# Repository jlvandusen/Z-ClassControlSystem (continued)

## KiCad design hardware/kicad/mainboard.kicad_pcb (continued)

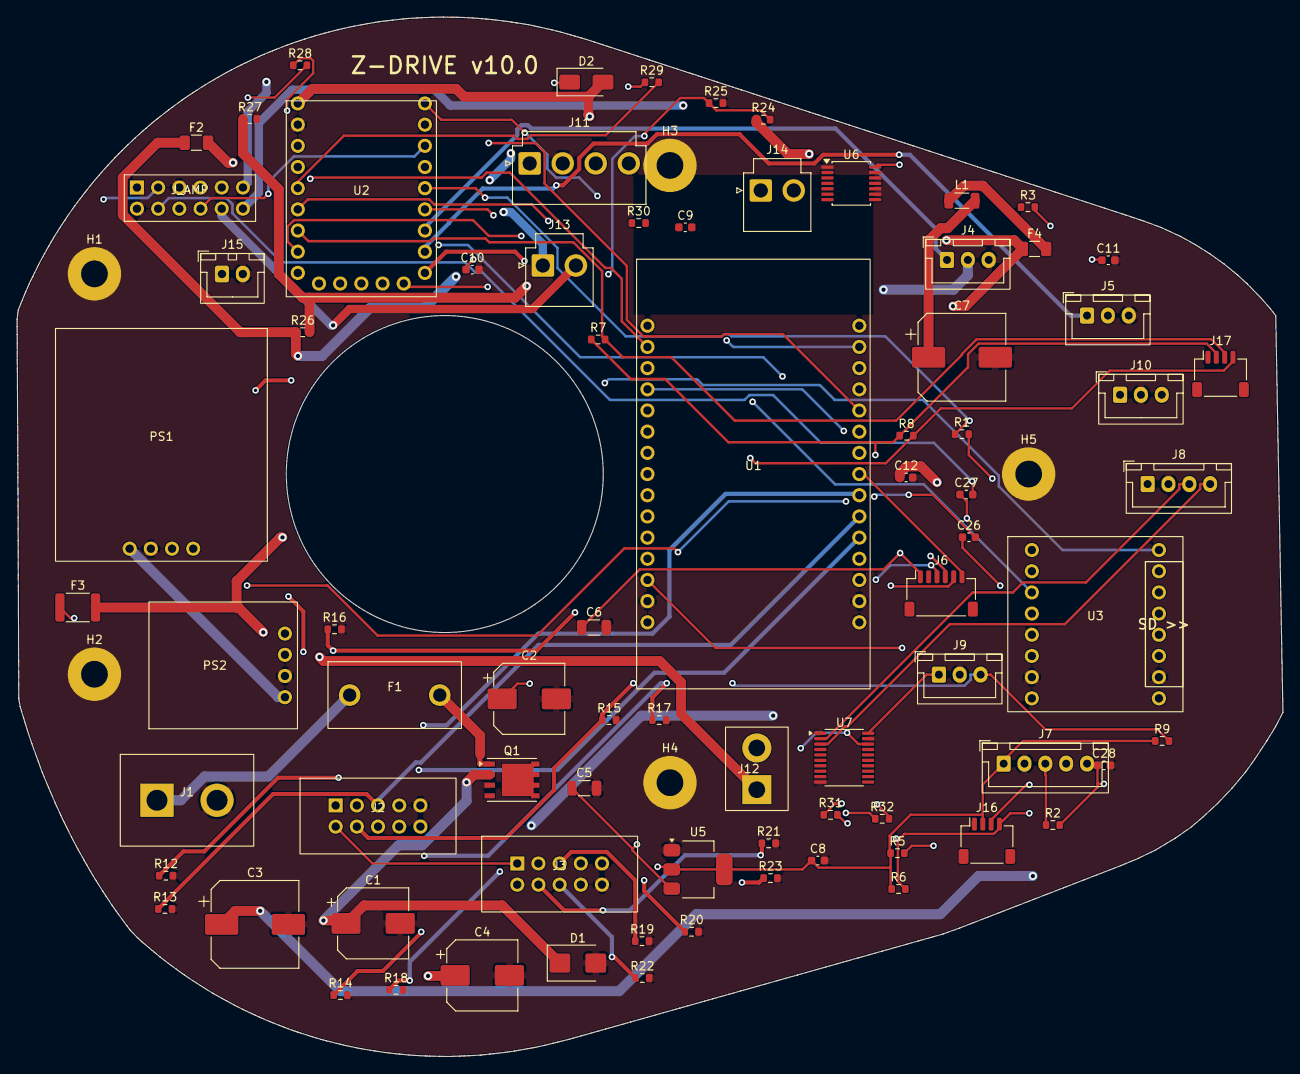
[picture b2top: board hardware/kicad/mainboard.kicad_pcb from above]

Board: 4 copper layers, 151.8 x 124.6 mm, 83 parts (0 on the bottom side), 67 nets.

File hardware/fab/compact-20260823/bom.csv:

Ref,Qty,Value / Part,MPN,Package,Supplier,Notes
U1,1,ESP-WROOM-32 DevKit (ELEGOO) - CUSTOMER FITS into J_U1A/J_U1B,ESP32-DevKit-V1 30-pin,plugs into 2x 1x15 sockets,Amazon B0D8T53CQ5,Drive MCU; 30-pin ONLY (38-pin is wider); antenna end toward H3
U2,1,Waveshare RP2350-Zero - CUSTOMER FITS into J_U2A/B/C,RP2350-Zero,plugs into 2x 1x9 + 1x5 sockets,Amazon B0DYTVCF2H,Body co-processor
U3,1,DFPlayer Mini,DFR0299,2x8 0.1in,DFRobot / AliExpress,SD MP3 source; socket
U4,1,MAX9744 class-D amp,MAX9744ETH+,TQFN-44 7x7,Digi-Key,2x20W I2C volume; thermal pad to pour
U5,1,3.3V 1A LDO,AMS1117-3.3,SOT-223,LCSC C6186,Pinout GND/OUT(tab)/IN as routed. Alt AP7361C-33ER-13 (SOT-223R, C3743528). NOT AP7361C-33E-13 (IN/GND/OUT - wrong for this board)
U6,1,NeoPixel level shifter,74AHCT125PW,TSSOP-14,Digi-Key,3.3->5V WS2812 data
U7,1,Encoder level shifter,74LVC245APW,TSSOP-20,Digi-Key,5V encoder A/B -> 3.3V (or 2x BSS138)
PS1,1,5V 5A buck module,Pololu D24V50F5,Pololu 5-pin row EN VIN GND GND OUT,Pololu 2851,+5V_LOGIC and +5V_LED
PS2,1,6V 2.5A buck module,Pololu D24V25F6,Pololu 5-pin row EN VIN GND GND OUT,Pololu 2852,+6V_SERVO: 6.0 V suits BOTH Hitec HS-805BB (4.8-6V) and JX PDI-HV2060MG (6-8.4V)
Q1,1,P-FET reverse polarity (high-side RPP),SI7461DP-T1-GE3,PowerPAK SO-8,Digi-Key,"-60V 14.5mOhm -14A; pads 1-3 S=VIN, 4 G, 5 tab D=BAT_F"
D1,1,TVS,SMBJ15A,SMB,Digi-Key,Input clamp 12V pack
D2,1,Schottky,SS14,SMA,Digi-Key,+5V_LOGIC -> RP2350-Zero 5V (USB back-feed block); pad1 K = RP_5V
D6,1,Zener 12V (Q1 gate clamp),BZT52C12-7-F,SOD-123,Digi-Key,VGS clamp S->G
D4,1,BAT54S,BAT54S,SOT-23,Digi-Key,ADC clamp on VBAT_SENSE (GPIO35); pin1 A->GND pin2 K->3V3 pin3 COM->sense
F1,1,Mini blade fuse holder + 10A ATM fuse,Keystone 3568 / 10A ATM,THT 9.9mm pitch,LCSC C5249699 / auto store,Board input (bucks + amp only; motors fed from the pack directly)
F3,1,Polyfuse 3A,MF-MSMF300,1812,Digi-Key,+5V_LED to slip ring
F4,1,Fuse 3A fast (amp 12V),0466003.NR,1206,Digi-Key,Littelfuse 466 series 32V
L1,1,Ferrite bead 600R@100MHz 2.9A,BLM31KN601SN1L,1206,LCSC C668306,Amp supply (PG variant is only 1.5 A)
C1,1,220uF 25V electrolytic,EEE-FK1E221P,SMD 8x10,Digi-Key,VIN
C2,1,470uF 10V,EEE-FK1A471P,SMD 8x10,Digi-Key,+5V_LOGIC
C3,1,1000uF 10V,EEE-FK1A102P,SMD 10x10,Digi-Key,+5V_LED
C4,1,470uF 16V,EEE-FK1C471P,SMD 8x10,Digi-Key,+6V_SERVO
C7,1,1000uF 25V,EEE-FP1E102AP,SMD 10x10.2,Digi-Key,MAX9744 supply (10mm can to match CP_Elec_10x10; verify height vs casing)
C5-C6,2,10uF 25V X7R,GRM31CR71E106KA12L,1206,Digi-Key,Rail local (+5V_LOGIC / +3V3)
C8-C25 + C29,19,100nF 50V X7R,CL10B104KB8NNNC,0603,Digi-Key,Decoupling; C29 = VBAT_SENSE ADC reservoir
C26-C27,2,1uF 16V X7R,CL10B105KO8NNNC,0603,Digi-Key,Audio input coupling
C28,1,100nF,CL10B104KB8NNNC,0603,Digi-Key,Pot / AS5600 OUT filter
R1,1,1k 1%,RC0603FR-071KL,0603,Digi-Key,DFPlayer TX series
R2,1,1k 1%,RC0603FR-071KL,0603,Digi-Key,Pot/AS5600 OUT series
R3-R4,2,330R 1%,RC0603FR-07330RL,0603,Digi-Key,NeoPixel data series (body + spare)
R5-R8,4,4.7k 1%,RC0603FR-074K7L,0603,Digi-Key,I2C pull-ups (ESP32 bus + RP2350 bus)
R9-R11,3,10k 1%,RC0603FR-0710KL,0603,Digi-Key,Hall / encoder pull-ups
R12-R23,12,10k 1%,RC0603FR-0710KL,0603,Digi-Key,Motor driver PWM/INA/INB pull-downs (4 ch x 3)
R24,1,47k 1%,RC0603FR-0747KL,0603,Digi-Key,Battery sense top
R25,1,10k 1%,RC0603FR-0710KL,0603,Digi-Key,Battery sense bottom
R28,1,10k 1%,RC0603FR-0710KL,0603,Digi-Key,ESTOP pull-up
R29-R30,2,10k 1%,RC0603FR-0710KL,0603,Digi-Key,+5V_LOGIC sense divider (RP2350 GP28)
R33,1,47k 1%,RC0603FR-0747KL,0603,Digi-Key,Q1 gate pull-down
J1,1,XT60 male PCB VERTICAL,XT60PB-M (Amass),THT 2x dia4.0 @ 7.2mm,LCSC C19268037 (alt JLC lib C9900017179),SINGLE board VCC input: 12 V 3S4P pack (9-12.6 V) -> F1 10A -> Q1 RPP -> VIN; pack lead = XT60 female
J_AMP,1,Pin header 2x7 0.1in male,PH2-14-UA,TH,Digi-Key,MAX9744 amp module harness: 1 VDD12 2 GND 3 INL 4 INR 5 AGND 6 SDA 7 SCL 8 SHDN 9-12 SPK L+/L-/R+/R- 13 Vi2c(3V3) 14 GND
J_U1A-J_U1B,2,Female header 1x15 2.54mm 8.5mm,B-2200S15P-A120 (Ckmtw),THT,LCSC C124408,ESP32 DevKitC sockets
J_U2A-J_U2B,2,Female header 1x9 2.54mm 8.5mm,B-2200S09P-A120 (Ckmtw),THT,LCSC C124417,RP2350-Zero side sockets (low stock: cut a 1x15 if out)
J_U2C,1,Female header 1x5 2.54mm 8.5mm,2.54-1*5P (BOOMELE),THT,LCSC C50950,RP2350-Zero end socket
J2-J3,2,Pin header 2x5 0.1in male (no shroud),PH2-10-UA,TH,Digi-Key,Motor driver IDC ribbons - odd pins = channel A row (VCC PWM INA INB GND); even = channel B
J4-J5,2,Pin header 1x3 0.1in,PH1-03-UA,TH,Digi-Key,Servos L / R (SIG +6V GND) - Hitec HS-805BB or JX PDI-HV2060MG jumbo servos
J6,1,JST-XH 4-pin,B4B-XH-A,XH TH,Digi-Key,IMU GY-BMI160 over I2C: 1 +5V->VIN, 2 GND, 3 SCL, 4 SDA (same order as v9.15 MPU)
J7,1,JST-XH 5-pin,B5B-XH-A,XH TH,Digi-Key,S2S sensor (3V3 GND OUT SDA SCL) - AS5600 or pot
J8,1,JST-XH 4-pin,B4B-XH-A,XH TH,Digi-Key,Dome encoder (B A GND 5V) - same order as v9.15 DOME_ENC
J9,1,JST-XH 3-pin,B3B-XH-A,XH TH,Digi-Key,Hall
J10,1,JST-XH 3-pin,B3B-XH-A,XH TH,Digi-Key,Body NeoPixel (5V GND DATA)
J11,1,JST-XH 2-pin,B2B-XH-A,XH TH,Digi-Key,Slip ring: +5V_LED / GND to body-shell NeoPixels (pack charges via its own lead - no charge path on board)
J13-J14,2,JST-VH 2-pin,B2P-VH,VH TH,Digi-Key,Speakers L / R (BTL)
J15,1,JST-XH 2-pin,B2B-XH-A,XH TH,Digi-Key,ESTOP loop
J17,1,JST-SH 4-pin (Qwiic),SM04B-SRSS-TB,SH SMD,Digi-Key,I2C expansion on the RP2350 bus (ESP32 bus is on J7 pins 4/5)
SW1,1,Tactile (RP2350 / board reset),PTS645SK50SMTR92,SMD,Digi-Key,Optional
TP1-TP10,10,Test points,5019,SMD,Digi-Key,3V3 5V_LOGIC 5V_LED 6V VIN UART x2 MOTOR_EN
H1-H4,4,M3 mounting holes,-,3.2mm,-,Reuse v9.15 pattern if on the deck
PCB,1,4-layer 1oz 1.6mm FR4 (F/In1 GND/In2 +5V/B),-,-,PCBWay,teardrop ~152x125 (extended) or ~152x110 (compact)

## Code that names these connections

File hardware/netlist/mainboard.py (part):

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A(dict(ref="J1", value="XT60PB-M vertical", kind="connector", fp="Connector_AMASS:AMASS_XT60-M_1x02_P7.20mm_Vertical",
       at=(-27, -31), rot=0, side="F", pins=[(1,"+","BAT+"),(2,"-","GND")]))
A(dict(ref="F1", value="10A blade fuse", kind="fuse", fp="ZCLASS:Fuse_Mini_Blade",
       at=(-13, -26.5), rot=0, side="F", pins=[(1,"1","BAT+"),(2,"2","BAT_F")]))
# High-side reverse-polarity P-FET. PowerPAK SO-8 pinout: pads 1,2,3 = SOURCE, 4 = GATE,
# 5 = DRAIN (tab). RPP orientation: D = battery side (BAT_F), S = load side (VIN);
# body diode pre-charges VIN, then VGS = -VIN enhances; a reversed pack is blocked.
# Si7461DP: -60 V, 14.5 mOhm, -14 A (SQJ431EP was 213 mOhm and an SO-8L part - wrong).
A(dict(ref="Q1", value="Si7461DP P-FET RPP", kind="ic3", fp="Package_SO:PowerPAK_SO-8_Single",
       at=(-1, -26), rot=0, side="F",
       pins=[(1,"S","VIN"),(2,"S","VIN"),(3,"S","VIN"),(4,"G","Q1_G"),(5,"D","BAT_F")]))
# gate protection: VGS clamped to -12 V (abs max +/-20 V; SMBJ15A can let VIN reach ~24 V)
A(two("D6", "BZT52C12 12V zener", "diode", "Diode_SMD:D_SOD-123", (-1, -22), "VIN", "Q1_G"))   # pin1 K = VIN (source), pin2 A = gate
A(two("R33", "47k", "res", "Resistor_SMD:R_0603_1608Metric", (3, -22), "Q1_G", "GND"))
A(two("D1", "SMBJ15A", "diode", "Diode_SMD:D_SMB", (8, -22.5), "VIN", "GND"))
A(two("C1", "220u/25V", "cap", "Capacitor_SMD:CP_Elec_8x10", (-32, -19), "VIN", "GND"))
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# ADC protection (GPIO35 is input-only, no internal clamps): BAT54S series pair in SOT-23,
# pin1 = A1 -> GND, pin2 = K2 -> +3V3, pin3 = common -> sense node. Plus 100n (SAR ADC charge reservoir).
A(dict(ref="D4", value="BAT54S", kind="ic3", fp="Package_TO_SOT_SMD:SOT-23", at=(47, 38), rot=0, side="F",
       pins=[(1,"A1","GND"),(2,"K2","+3V3"),(3,"COM","VBAT_SENSE")]))
A(two("C29", "100n", "cap", "Capacitor_SMD:C_0603_1608Metric", (44, 37), "VBAT_SENSE", "GND"))
# ---- 5V / 3V3 rail parts
A(two("C2", "470u/10V", "cap", "Capacitor_SMD:CP_Elec_8x10", (-26, -19), "+5V_LOGIC", "GND"))
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# ---- servos: 6.0 V rail = the one voltage both the Hitec HS-805BB (4.8-6.0 V) and the
#      JX PDI-HV2060MG (6.0-8.4 V) accept. Both are jumbo (1/4-scale) cases.
A(dict(ref="J4", value="Servo L", kind="connector", fp="Connector_PinHeader_2.54mm:PinHeader_1x03_P2.54mm_Vertical",
       at=(55, 21), rot=0, side="F", pins=[(1,"SIG","SERVO_L"),(2,"6V","+6V_SERVO"),(3,"GND","GND")]))
A(dict(ref="J5", value="Servo R", kind="connector", fp="Connector_PinHeader_2.54mm:PinHeader_1x03_P2.54mm_Vertical",
       at=(66, 19), rot=0, side="F", pins=[(1,"SIG","SERVO_R"),(2,"6V","+6V_SERVO"),(3,"GND","GND")]))
# ---- IMU (I2C, 4-pin JST-XH like v9.15)
# IMU: GY-BMI160 breakout over I2C (ESP32 I2C-A bus, shared with the AS5600 - addr 0x68/0x69 vs 0x36).
# JST-XH 4-pin in the SAME order as the v9.15 "MPU" connector: VCC GND sig sig -> the old cable fits.
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# CS / SA0 left open -> I2C mode. The ESP32 SPI pins (D5/D18/D19/D23) are now spare.
A(dict(ref="J6", value="IMU BMI160 I2C", kind="connector", fp="Connector_JST:JST_XH_B4B-XH-A_1x04_P2.50mm_Vertical",
       at=(57, -24), rot=0, side="F",
       pins=[(1,"5V","+5V_LOGIC"),(2,"GND","GND"),(3,"SCL","I2C_A_SCL"),(4,"SDA","I2C_A_SDA")]))
# ---- S2S sensor (AS5600 or pot): 3V3 GND OUT SDA SCL
A(dict(ref="J7", value="S2S AS5600/pot", kind="connector", fp="Connector_JST:JST_XH_B5B-XH-A_1x05_P2.50mm_Vertical",
       at=(70, -19), rot=0, side="F",
       pins=[(1,"3V3","+3V3"),(2,"GND","GND"),(3,"OUT","S2S_OUT"),(4,"SDA","I2C_A_SDA"),(5,"SCL","I2C_A_SCL")]))
A(two("R2", "1k", "res", "Resistor_SMD:R_0603_1608Metric", (64, -30), "S2S_OUT", "S2S_POS"))
A(two("C28", "100n", "cap", "Capacitor_SMD:C_0603_1608Metric", (67, -30), "S2S_POS", "GND"))
# ---- dome encoder (5V) -> 74LVC245 -> 3V3
#   pin order kept IDENTICAL to the v9.15 DOME_ENC header (B, A, GND, VCC) so the
#   existing NeveRest encoder cable plugs straight in — do not reorder.
A(dict(ref="J8", value="Dome encoder", kind="connector", fp="Connector_JST:JST_XH_B4B-XH-A_1x04_P2.50mm_Vertical",
       at=(82, -14), rot=0, side="F", pins=[(1,"B","ENC_B_5V"),(2,"A","ENC_A_5V"),(3,"GND","GND"),(4,"5V","+5V_LOGIC")]))
A(dict(ref="U7", value="74LVC245A", kind="ic_generic", fp="Package_SO:TSSOP-20_4.4x6.5mm_P0.65mm",
       at=(30, -32), rot=0, side="F",
       # DIR HIGH = A->B (TI SN74LVC245A pin table). Encoder 5V sits on A1/A2, RP2350 on B1/B2, so DIR
       # must be +3V3 — it was GND (B->A) on the first rev-A gerbers (r6); fixed in r7. Unused A3..A8
       # are inputs when DIR=H, so they are tied to GND rather than left floating.
       pins=[(1,"DIR","+3V3"),(2,"A1","ENC_A_5V"),(3,"A2","ENC_B_5V"),(4,"A3","GND"),(5,"A4","GND"),(6,"A5","GND"),(7,"A6","GND"),(8,"A7","GND"),(9,"A8","GND"),
             (10,"GND","GND"),(11,"B8","NC"),(12,"B7","NC"),(13,"B6","NC"),(14,"B5","NC"),(15,"B4","NC"),(16,"B3","NC"),(17,"B2","ENC_B_3V3"),(18,"B1","ENC_A_3V3"),
             (19,"OE","GND"),(20,"VCC","+3V3")]))
A(two("C8", "100n", "cap", "Capacitor_SMD:C_0603_1608Metric", (30, -36), "+3V3", "GND"))
# ---- hall
A(dict(ref="J9", value="Hall", kind="connector", fp="Connector_JST:JST_XH_B3B-XH-A_1x03_P2.50mm_Vertical",
       at=(60, -30), rot=0, side="F", pins=[(1,"3V3","+3V3"),(2,"GND","GND"),(3,"SIG","HALL")]))
A(two("R9", "10k", "res", "Resistor_SMD:R_0603_1608Metric", (86, -30), "+3V3", "HALL"))
# ---- body NeoPixel: GP14 -> 74AHCT125 -> 330R -> J10
A(dict(ref="U6", value="74AHCT125", kind="ic_generic", fp="Package_SO:TSSOP-14_4.4x5mm_P0.65mm",
       at=(40, 30), rot=0, side="F",
       pins=[(1,"1OE","GND"),(2,"1A","NEO_3V3"),(3,"1Y","NEO_5V"),(4,"2OE","GND"),(5,"2A","GND"),(6,"2Y","NC"),(7,"GND","GND"),
             (8,"3Y","NC"),(9,"3A","GND"),(10,"3OE","GND"),(11,"4Y","NC"),(12,"4A","GND"),(13,"4OE","GND"),(14,"VCC","+5V_LOGIC")]))
A(two("C9", "100n", "cap", "Capacitor_SMD:C_0603_1608Metric", (40, 34), "+5V_LOGIC", "GND"))
A(two("R3", "330R", "res", "Resistor_SMD:R_0603_1608Metric", (47, 30), "NEO_5V", "NEO_OUT"))
A(dict(ref="J10", value="Body NeoPixel", kind="connector", fp="Connector_JST:JST_XH_B3B-XH-A_1x03_P2.50mm_Vertical",
       at=(77, 14), rot=0, side="F", pins=[(1,"5V","+5V_LED"),(2,"GND","GND"),(3,"DATA","NEO_OUT")]))
# ---- slip ring: +5V_LED + GND out to the body-shell NeoPixels only.
#      (The pack charges through its OWN charge lead, routed out through the axle -
#       the board carries no charge path and no charger sense.)
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       at=(-30, 38), rot=0, side="F", pins=[(1,"+","SPK_R+"),(2,"-","SPK_R-")]))
# ---- ESTOP loop
A(dict(ref="J15", value="ESTOP", kind="connector", fp="Connector_JST:JST_XH_B2B-XH-A_1x02_P2.50mm_Vertical",
       at=(6, 47), rot=0, side="F", pins=[(1,"LOOP","ESTOP_SENSE"),(2,"GND","GND")]))
A(two("R28", "10k", "res", "Resistor_SMD:R_0603_1608Metric", (-30, 46), "+3V3", "ESTOP_SENSE"))
# ---- I2C expansion (Qwiic-style SH) on both buses
# (I2C-A expansion J16 removed: the ESP32 bus is already exposed on J7 pins 4/5 for the AS5600;
#  J17 on the RP2350 bus is the single expansion port.)
A(dict(ref="J17", value="I2C-B exp (RP2350)", kind="connector", fp="Connector_JST:JST_SH_SM04B-SRSS-TB_1x04-1MP_P1.00mm_Horizontal",
       at=(87, 12), rot=0, side="F", pins=[(1,"GND","GND"),(2,"3V3","+3V3"),(3,"SDA","I2C_B_SDA"),(4,"SCL","I2C_B_SCL")]))
A(two("R5", "4.7k", "res", "Resistor_SMD:R_0603_1608Metric", (58, -33), "+3V3", "I2C_A_SDA"))
A(two("R6", "4.7k", "res", "Resistor_SMD:R_0603_1608Metric", (61, -33), "+3V3", "I2C_A_SCL"))
A(two("R7", "4.7k", "res", "Resistor_SMD:R_0603_1608Metric", (40, 24), "+3V3", "I2C_B_SDA"))
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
